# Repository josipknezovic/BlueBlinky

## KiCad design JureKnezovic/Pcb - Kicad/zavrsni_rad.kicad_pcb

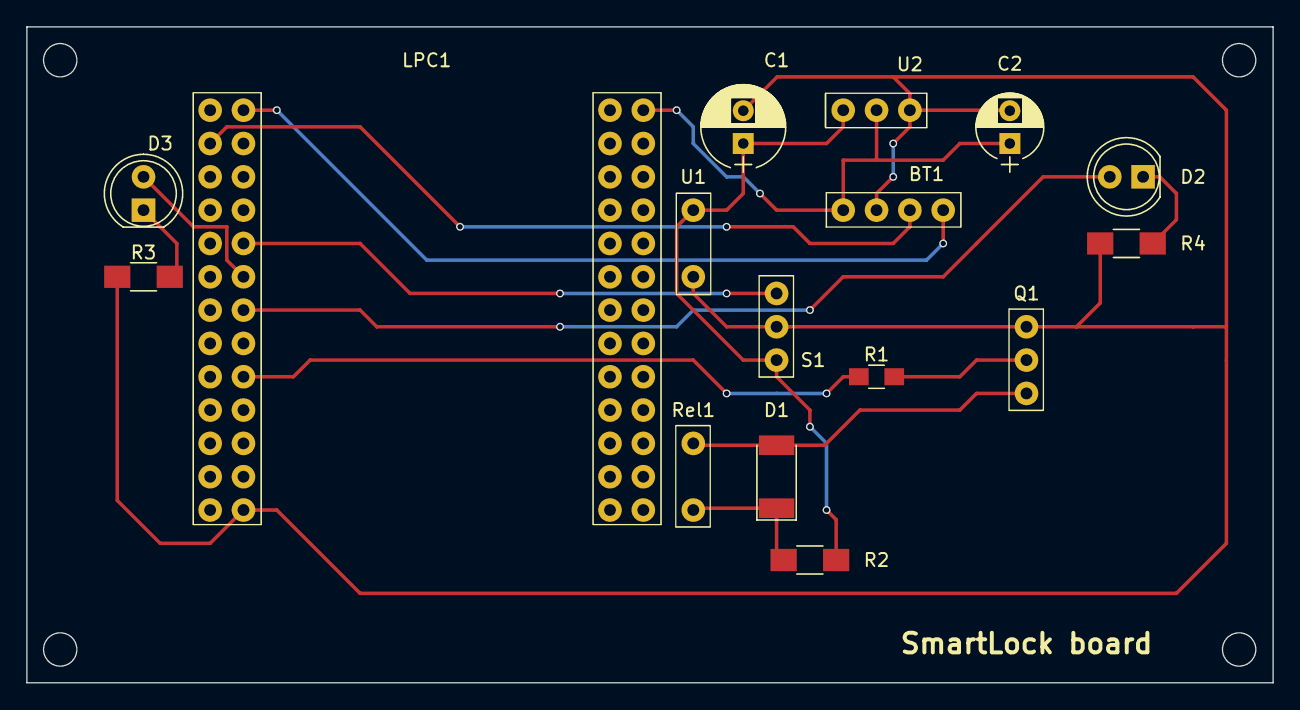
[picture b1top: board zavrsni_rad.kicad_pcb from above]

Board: 2 copper layers, 95.0 x 50.0 mm, 16 parts (0 on the bottom side), 14 nets.

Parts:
BT1: BluetoothHC06; FourPinConnector
C1: 100uF/16V; CP_Radial_D6.3mm_P2.50mm
C2: 10uF/16V; CP_Radial_D5.0mm_P2.50mm
D1: Dioda; D_MELF_Standard
D2: Crvena_led; LED_D5.0mm
D3: Zelena_LED; LED_D5.0mm
LPC1: ZP2148
Q1: NPN
R1: 4k7; R_0805_HandSoldering
R2: 68; R_1206_HandSoldering
R3, R4: 1K; R_1206_HandSoldering
Rel1: Relay; TwoPinConnector
S1: PIRsensor; ThreePinConnector
U1: PoE; TwoPinConnector
U2: LM1117-3.3V; ThreePinConnector

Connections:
+3V3: BT1.1, C2.1, LPC1.52, U2.2
CrvenaLed: D2.2, LPC1.14
GND: BT1.2, C1.2, C2.2, LPC1.26, Q1.3, R3.1, R4.1, S1.2, U1.2, U2.1
unnamed: D1.1, R2.2, Rel1.1
unnamed: D1.2, Q1.2, Rel1.2
unnamed: D2.1, R4.2
unnamed: D3.1, R3.2
unnamed: Q1.1, R1.1
Relej: LPC1.18, R1.2
RxD: BT1.3, LPC1.3
SenzorPokreta: LPC1.10, S1.3
TxD: BT1.4, LPC1.2
VCC: C1.1, R2.1, S1.1, U1.1, U2.3
ZelenaLed: D3.2, LPC1.12

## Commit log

2016-04-29 test
2016-04-29 dodan uVison projekt u repo.
2016-05-05 Dodana dokumentacija.
2016-05-06 Dokumentacija za produkcijsku pločicu LPC2148.
2016-05-06 Tranzistor za izlaz prema releju.
2016-05-09 Move.
2016-05-09 Dodana android aplikacija
2016-05-09 Dodane promjene u uVision
2016-05-31 uVision projekt za lpc2148
2016-05-31 Dodan widget.
2016-06-04 Regulator napajanja - datasheet.
2016-06-04 Regulator 3.3V - datasheet.
2016-06-05 Dodan Altium Designer projekt
2016-06-14 Dodan timer za delay umjesto for petlje
2016-06-21 Dodane promjene u Altium Designer projekt
2016-11-11 senzor pokreta
2016-11-11 preimenovan altium projekt dir
2017-01-23 Jure Knezovic
2017-01-23 Rjesenje projekta i projektna dokumentacija
2017-04-09 Dodana shema pločice u KiCad-u te programski kod za LPC
2017-04-10 Dodana android aplikacija i ažuriran kod za pločicu
